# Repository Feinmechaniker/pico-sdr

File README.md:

This repository holds files relevant to the PiCo Rx project - a design by Jon Dawson 
(see: https://101-things.readthedocs.io/en/latest/breadboard_radio.html ).
I adopted this wonderful idea from Jon to customize the hardware to my liking.

my current circuit diagram

current circuit board (Top-Side)

current circuit board (Bottom-Side)

current Band-pass filter

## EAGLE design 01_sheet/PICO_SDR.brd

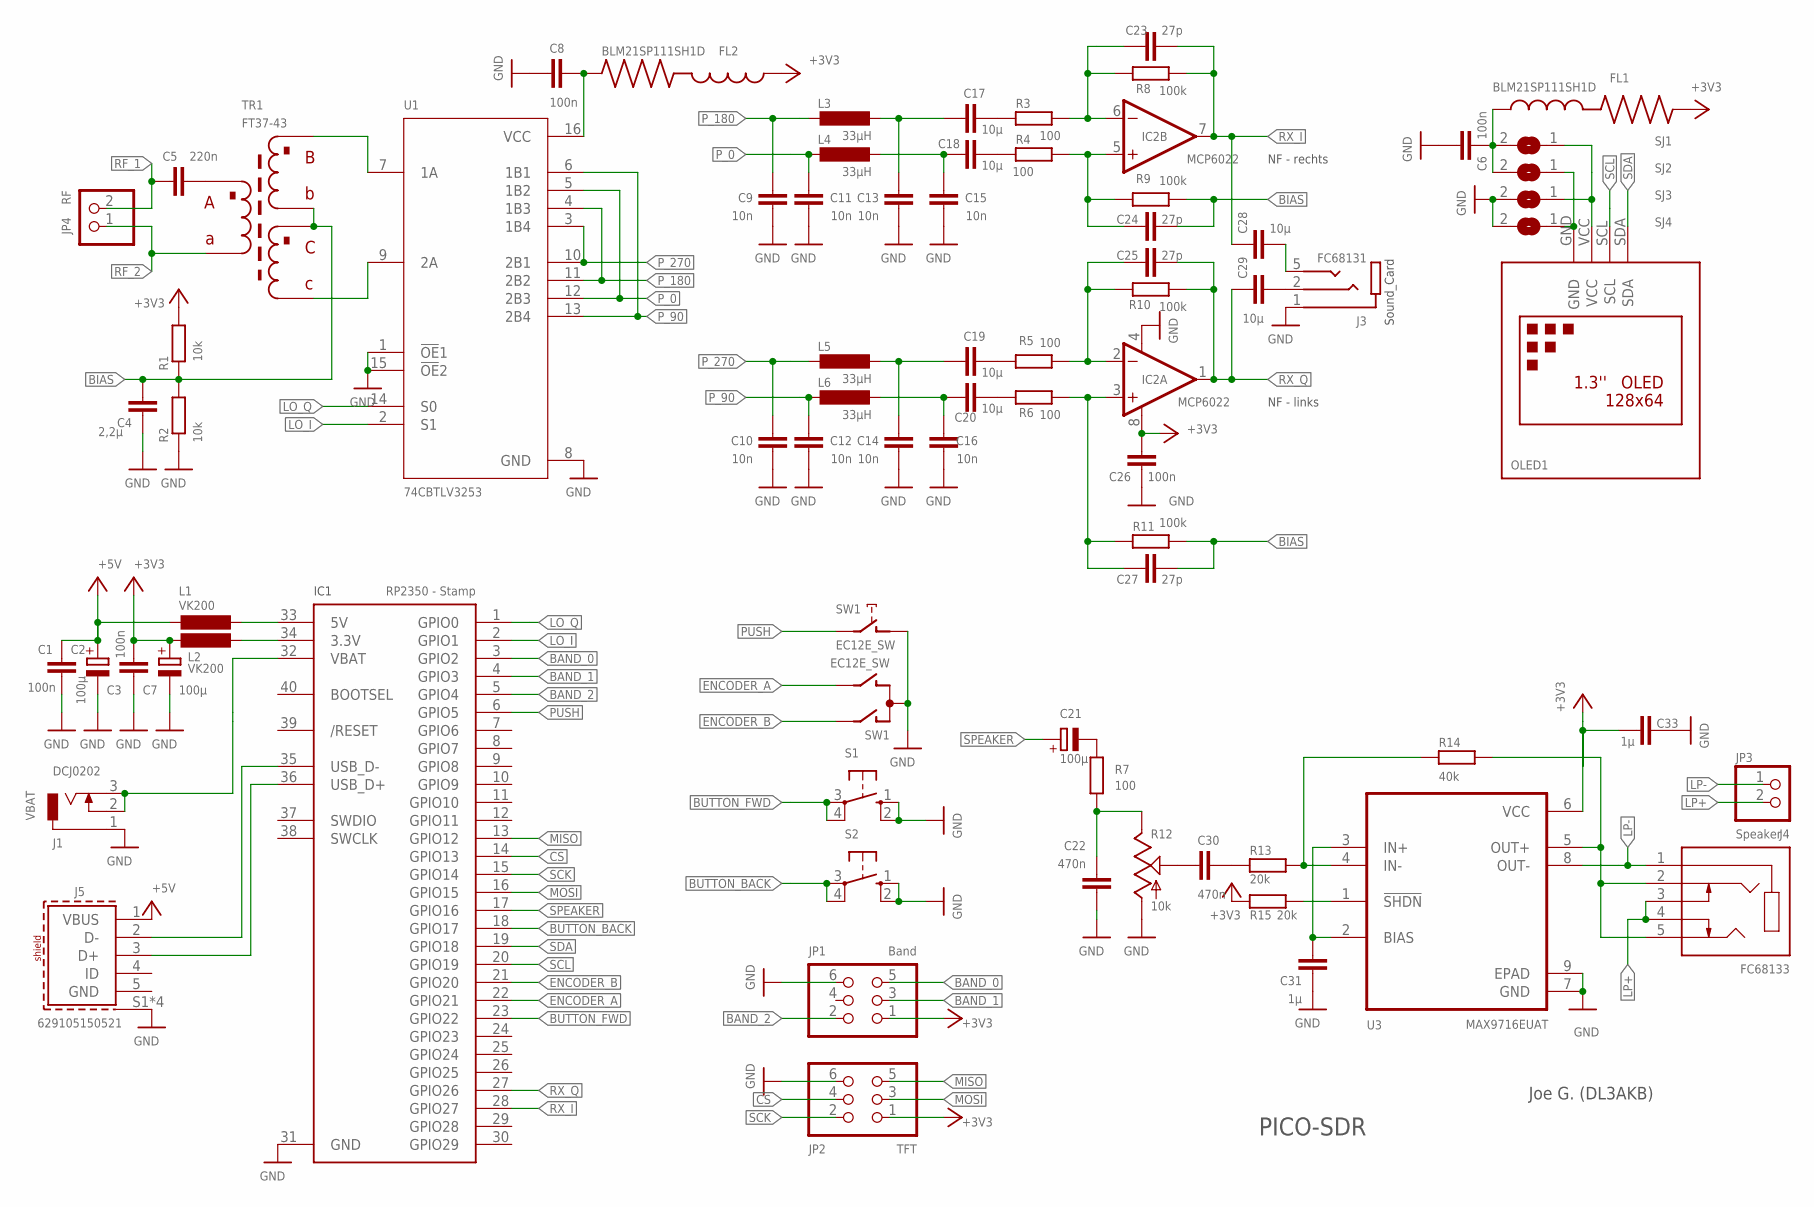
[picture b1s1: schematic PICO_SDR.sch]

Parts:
C1, C3: 100n; C1206
C2, C7, C21: 100µ; SMC_D
C4: 2,2µ; C0805
C5: 220n; C1206
C6, C8, C26: 100n; C0805
C9, C10, C11, C12, C13, C14, C15, C16: 10n; C0805
C17, C18, C19, C20, C28, C29: 10µ; C1206
C22: 470n; C1206
C23, C24, C25, C27: 27p; C1206
C30: 470n; C0805
C31: 1µ; C0805
C33: 1µ; C1206
FL1, FL2: BLM21SP111SH1D; BEADC2012X105N
IC1: RP2350 - Stamp; RP2XXX_STAMP_SMD
IC2: MCP6022; SO08
J1: DCJ0202
J3: FC68131; CLIFF_FC68131
J4: FC68133; CLIFF_FC68133
J5: 629105150521
JP1: Band; 2X03
JP2: TFT; 2X03
JP3: Speaker; 1X02
JP4: RF; 1X02
L1, L2: VK200; 0207/5V
L3, L4, L5, L6: 33µH; L1812
OLED1: OLED; 1.3
R1, R2: 10k; R0805
R3, R4, R5, R6, R7: 100; R0805
R8, R9, R10, R11: 100k; R0805
R12: 10k; RK09K1130A6S
R13, R15: 20k; R0805
R14: 40k; R0805
S1, S2: 10-XX; B3F-10XX
SJ1, SJ2, SJ3, SJ4: SJ
SW1: EC12E_SW; ALPS_EC12E_SW
TR1: FT37-43
U1: 74CBTLV3253; SOIC127P599X175-16N
U3: MAX9716EUAT; SOP65P490X110-9N

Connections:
+3V3: C3.2, C7.+, C26.2, C33.2, FL1.2, FL2.1, IC2.8 (V+), JP1.1, JP2.1, L2.2, R1.2, R15.2, U3.6 (VCC)
+5V: C1.2, C2.+, J5.1 (VBUS), L1.2
BAND_0: IC1.3 (GPIO2), JP1.5
BAND_1: IC1.4 (GPIO3), JP1.3
BAND_2: IC1.5 (GPIO4), JP1.2
BIAS: C4.2, C24.2, C27.2, R1.1, R2.2, R9.1, R11.1, TR1.P$3, TR1.P$5
BUTTON_BACK: IC1.18 (GPIO17), S2.3, S2.4 (P1)
BUTTON_FWD: IC1.23 (GPIO22), S1.3, S1.4 (P1)
CS: IC1.14 (GPIO13), JP2.4
D+: IC1.36 (USB_D+), J5.3 (D+)
D-: IC1.35 (USB_D-), J5.2 (D-)
ENCODER_A: IC1.22 (GPIO21), SW1.B
ENCODER_B: IC1.21 (GPIO20), SW1.A
GND: C1.1, C2.-, C3.1, C4.1, C6.2, C7.-, C8.2, C9.1, C10.1, C11.1, C12.1, C13.1, C14.1, C15.1, C16.1, C22.1, C26.1, C31.1, C33.1, IC1.31 (GND), IC2.4 (V-), J1.1, J3.1 (SLEEVE), J5.S1 (SHIELD), J5.S2 (SHIELD), J5.S3 (SHIELD), J5.S4 (SHIELD), JP1.6, JP2.6, R2.1, R12.E (3), S1.1 (S), S1.2 (S1), S2.1 (S), S2.2 (S1), SJ3.2, SJ4.2, SW1.C, SW1.D (1), U1.1 (!OE!1), U1.8 (GND), U1.15 (!OE!2), U3.7 (GND), U3.9 (EPAD)
LO_I: IC1.2 (GPIO1), U1.2 (S1)
LO_Q: IC1.1 (GPIO0), U1.14 (S0)
LP+: J4.3, J4.4, JP3.2
LP-: J4.1, JP3.1, U3.8 (OUT-)
MISO: IC1.13 (GPIO12), JP2.5
MOSI: IC1.16 (GPIO15), JP2.3
unnamed: IC1.34 (3.3V), L2.1
unnamed: C21.-, R7.2
unnamed: C16.2, C20.1, L6.2
unnamed: IC1.33 (5V), L1.1
unnamed: TR1.P$6, U1.9 (2A)
unnamed: C19.2, R5.2
unnamed: TR1.P$2, U1.7 (1A)
unnamed: R13.1, R14.2, U3.4 (IN-)
unnamed: C30.2, R12.S (2)
unnamed: C27.1, IC2.3 (+IN), R6.1, R11.2
unnamed: C25.1, IC2.2 (-IN), R5.1, R10.2
unnamed: C18.2, R4.2
unnamed: C23.1, IC2.6 (-IN), R3.1, R8.2
unnamed: C31.2, U3.2 (BIAS), U3.3 (IN+)
unnamed: C17.2, R3.2
unnamed: C24.1, IC2.5 (+IN), R4.1, R9.2
unnamed: C30.1, R13.2
unnamed: C5.2, TR1.P$1
unnamed: C20.2, R6.2
unnamed: C15.2, C18.1, L4.2
unnamed: C28.2, J3.5 (TIP)
unnamed: C29.2, J3.2 (RING)
unnamed: OLED1.GND, SJ2.1, SJ4.1
unnamed: OLED1.VCC, SJ1.1, SJ3.1
unnamed: R15.1, U3.1 (!SHDN)
unnamed: C13.2, C17.1, L3.2
unnamed: C14.2, C19.1, L5.2
unnamed: C6.1, FL1.1, SJ1.2, SJ2.2
unnamed: C8.1, FL2.2, U1.16 (VCC)
NF: C22.2, R7.1, R12.A (1)
OUT_R: J4.2, J4.5, R14.1, U3.5 (OUT+)
PUSH: IC1.6 (GPIO5), SW1.E (2)
P_0: C11.2, L4.1, U1.5 (1B2), U1.12 (2B3)
P_90: C12.2, L6.1, U1.6 (1B1), U1.13 (2B4)
P_180: C9.2, L3.1, U1.4 (1B3), U1.11 (2B2)
P_270: C10.2, L5.1, U1.3 (1B4), U1.10 (2B1)
RF_1: C5.1, JP4.2
RF_2: JP4.1, TR1.P$4
RX_I: C23.2, C28.1, IC1.28 (GPIO27), IC2.7 (OUT), R8.1
RX_Q: C25.2, C29.1, IC1.27 (GPIO26), IC2.1 (OUT), R10.1
SCK: IC1.15 (GPIO14), JP2.2
SCL: IC1.20 (GPIO19), OLED1.SCL
SDA: IC1.19 (GPIO18), OLED1.SDA
SPEAKER: C21.+, IC1.17 (GPIO16)
VBAT: IC1.32 (VBAT), J1.2, J1.3

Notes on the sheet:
Sound_Card
NF - links
NF - rechts
PICO-SDR
Joe G. (DL3AKB)

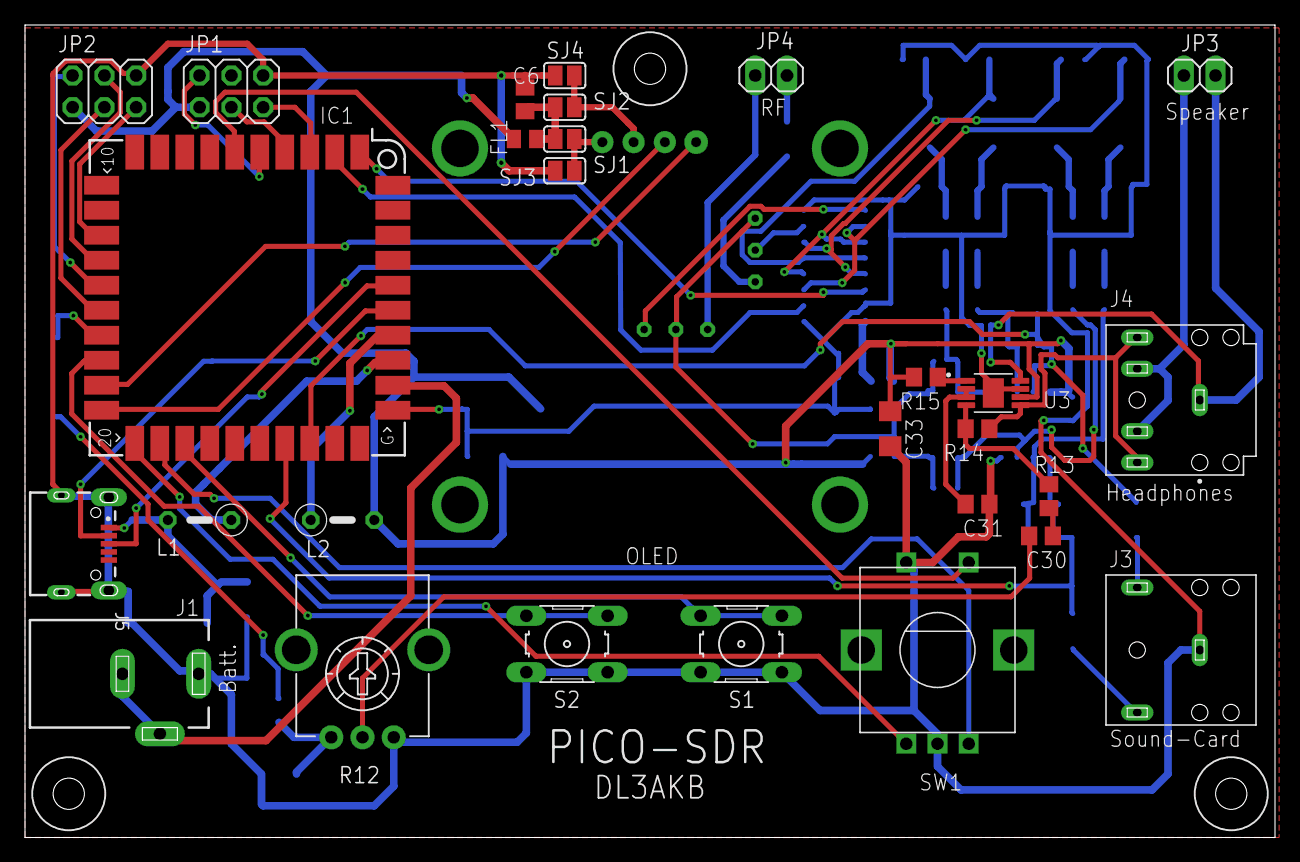
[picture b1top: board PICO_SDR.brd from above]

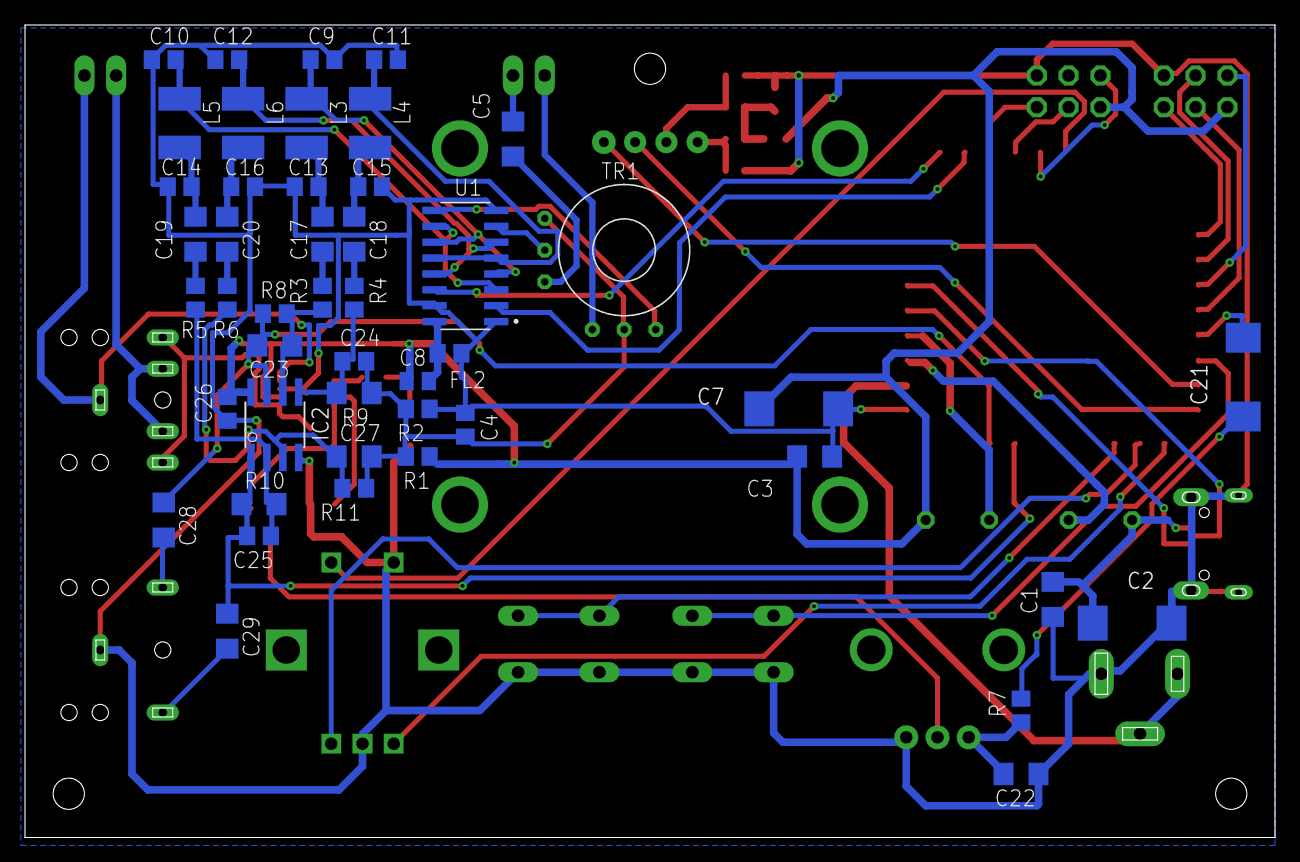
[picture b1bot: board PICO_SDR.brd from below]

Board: 2 copper layers, 99.9 x 64.9 mm, 79 parts (47 on the bottom side), 65 nets.

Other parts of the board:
U$8, U$9, U$10: DRIL-2,5

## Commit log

2025-05-19 sheet
2025-05-19 RP2350 pin usage
2025-05-19 memory upload
2025-05-19 QSD Simulation
2025-05-19 Firmware uf2 - File
2025-05-19 readme
2025-05-19 EAGLE Board
2025-05-20 new version
2025-05-20 LP Picture
2025-07-08 new Version (08.07.25)
2025-07-09 figure Band-pass filter
2025-07-09 BP LTSpice

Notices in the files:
parts and their libraries:
Eagle_WR-USB: Copyright: Würth Elektronik
